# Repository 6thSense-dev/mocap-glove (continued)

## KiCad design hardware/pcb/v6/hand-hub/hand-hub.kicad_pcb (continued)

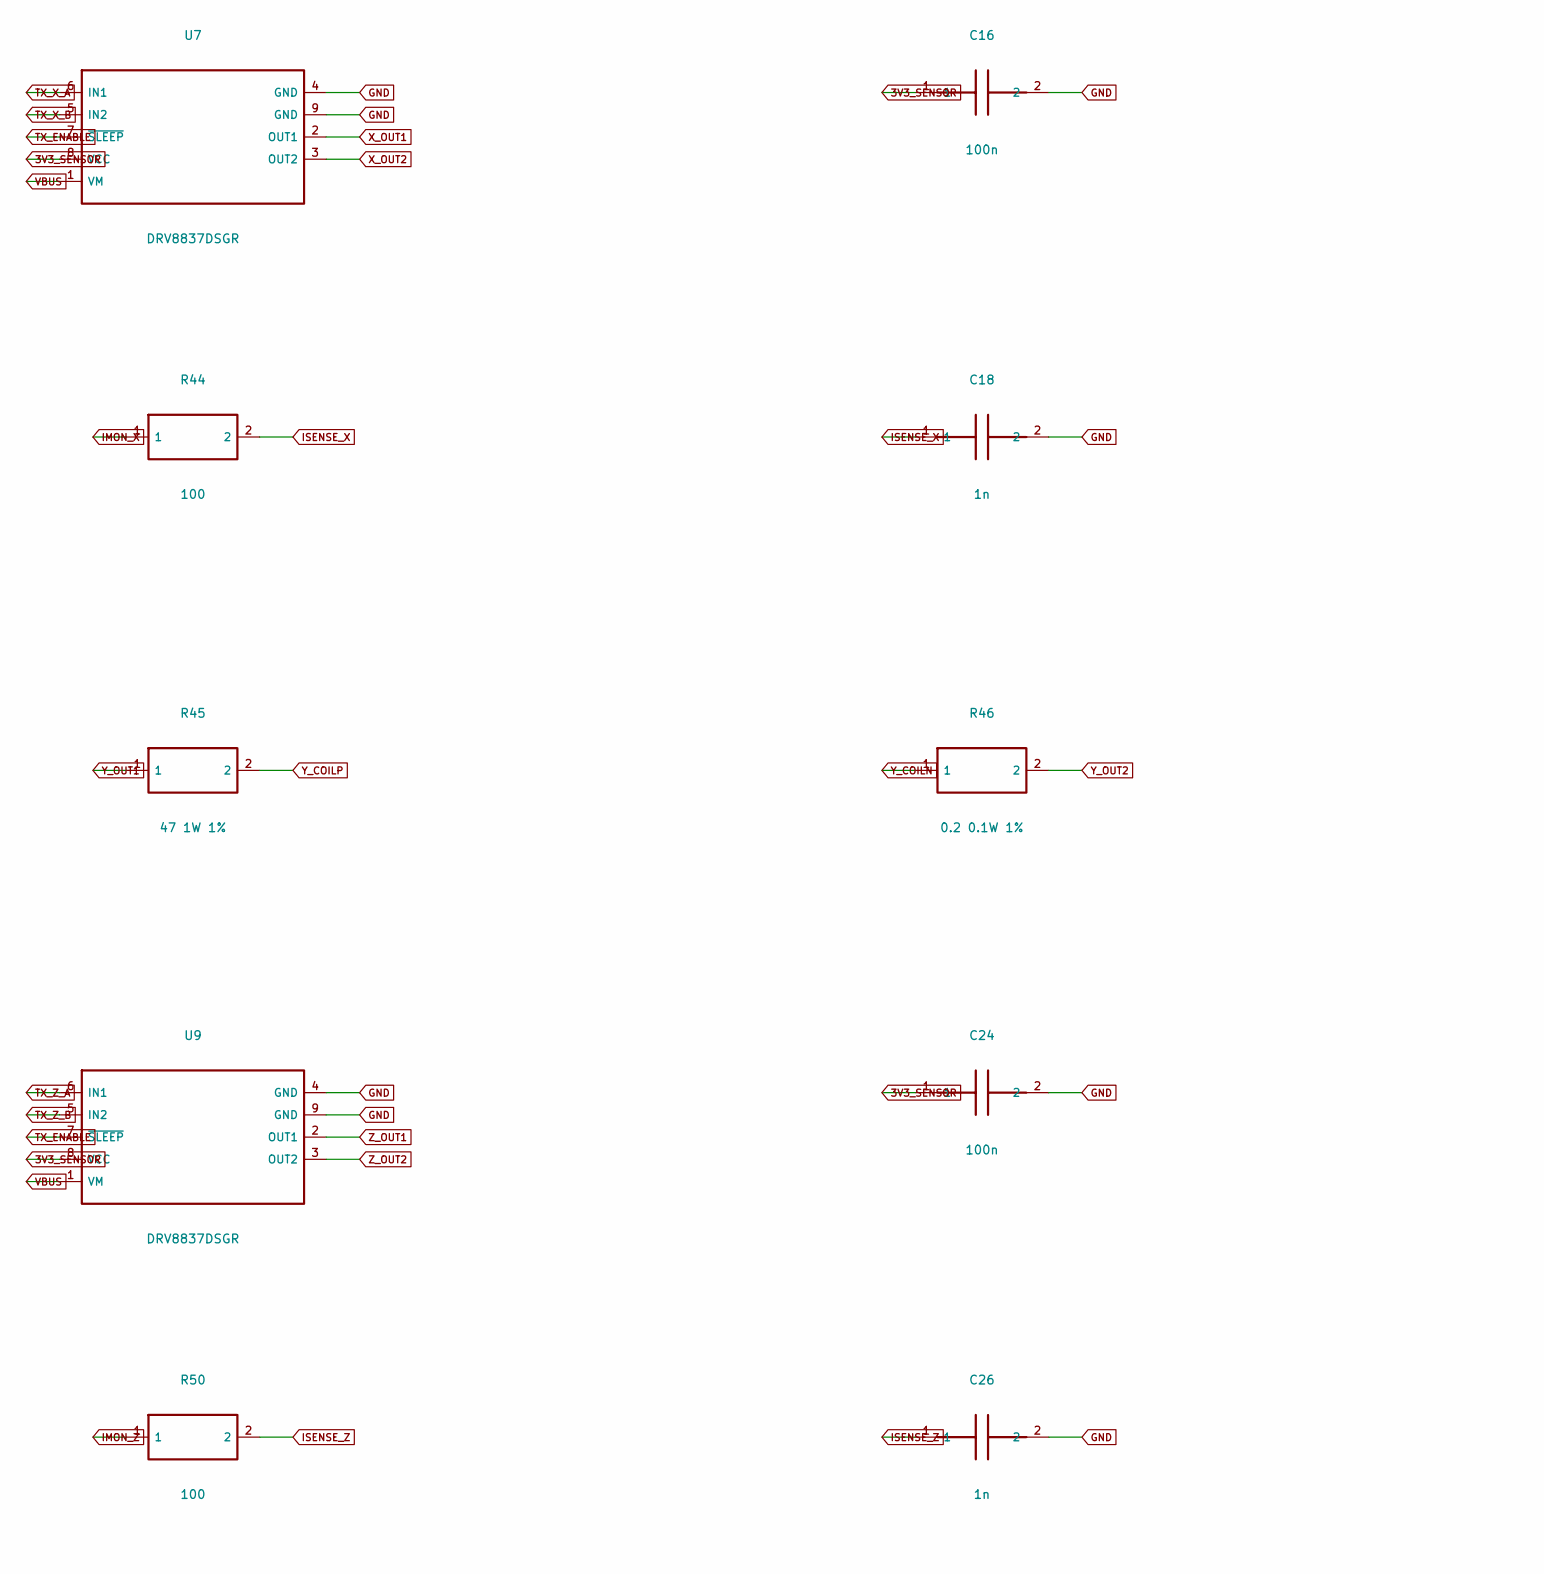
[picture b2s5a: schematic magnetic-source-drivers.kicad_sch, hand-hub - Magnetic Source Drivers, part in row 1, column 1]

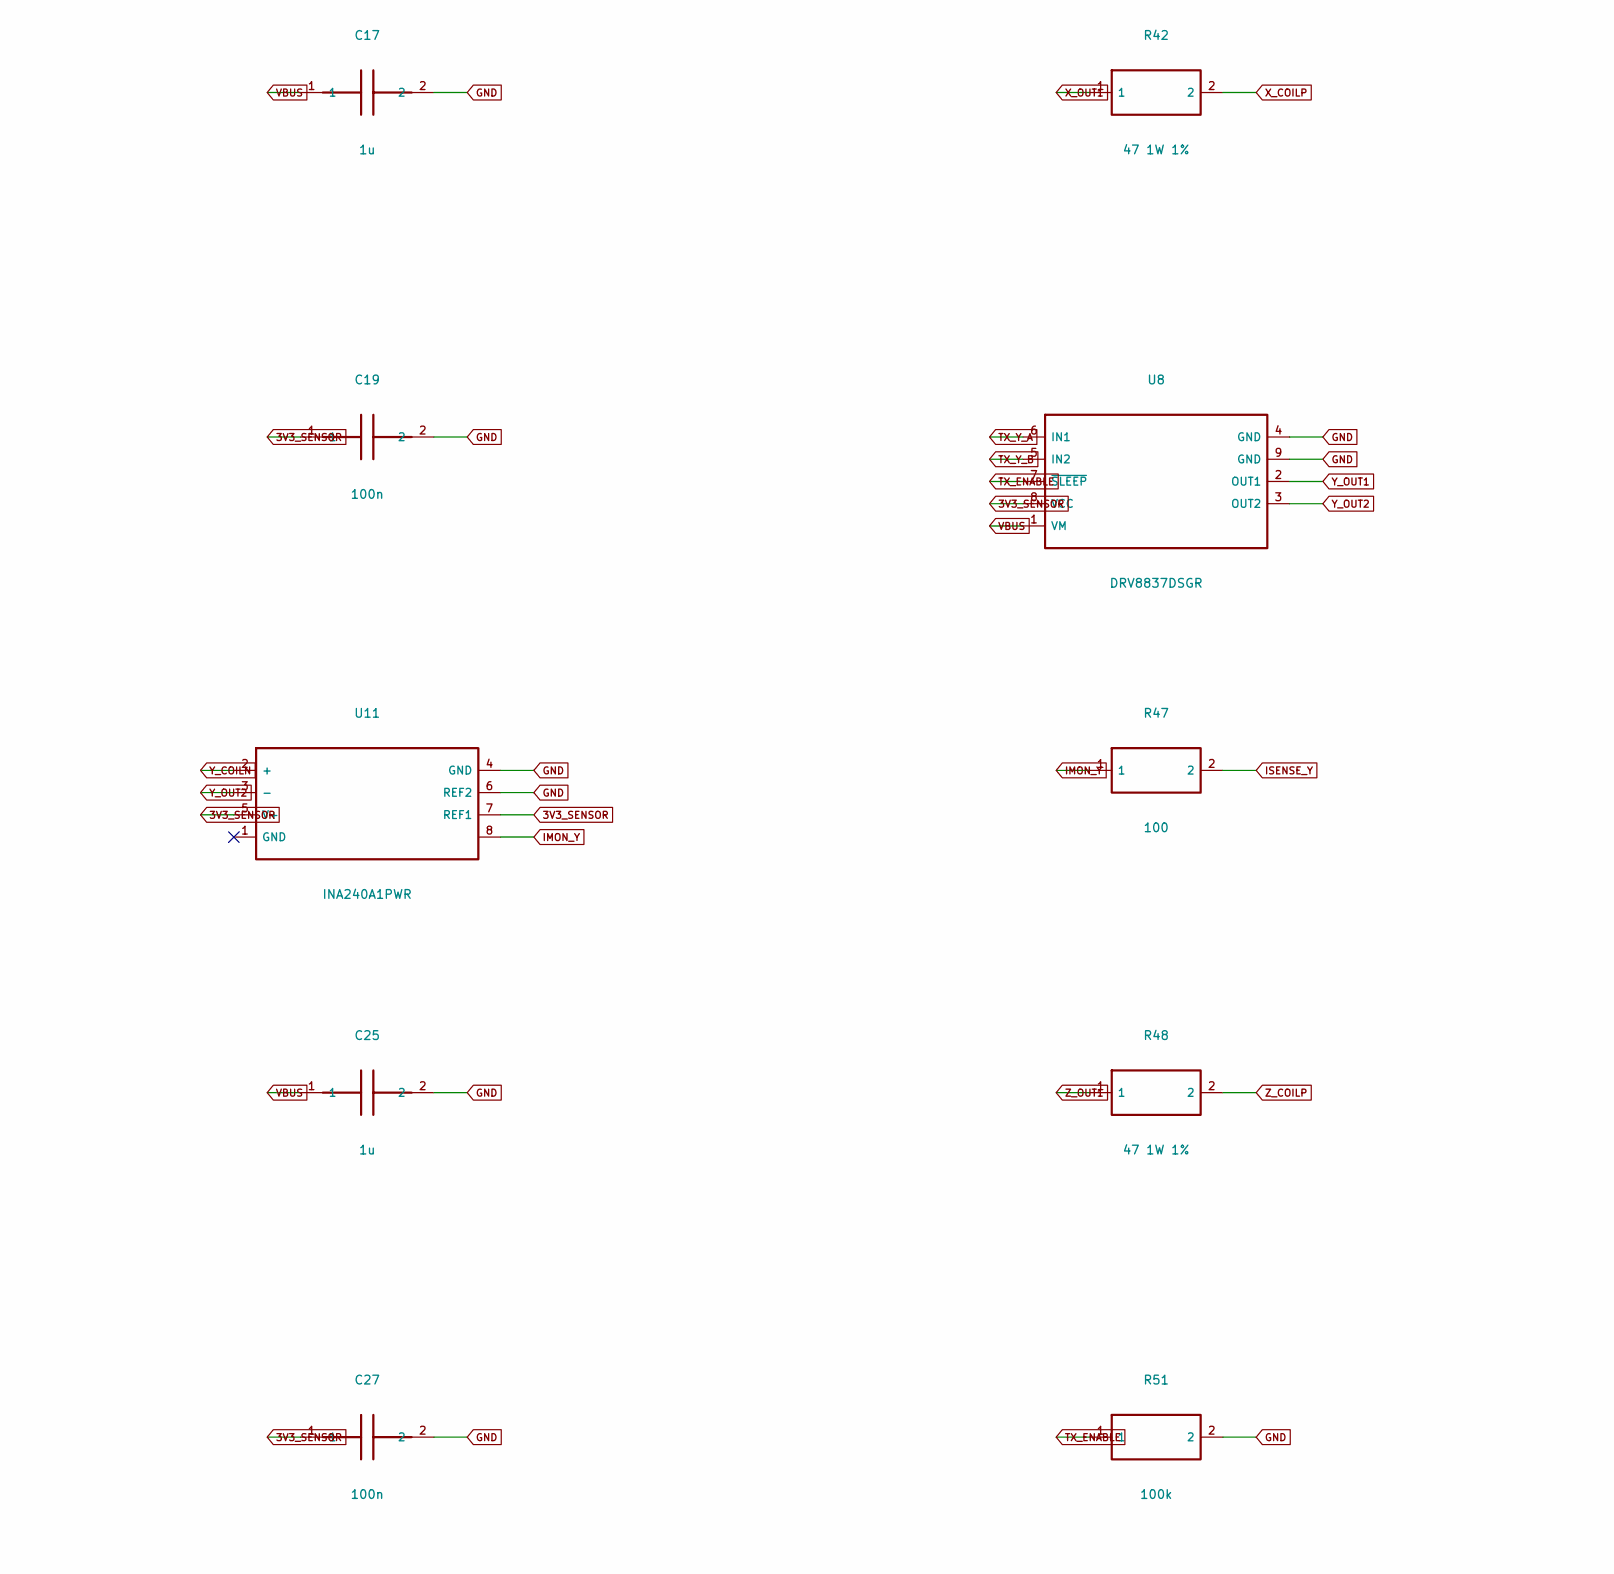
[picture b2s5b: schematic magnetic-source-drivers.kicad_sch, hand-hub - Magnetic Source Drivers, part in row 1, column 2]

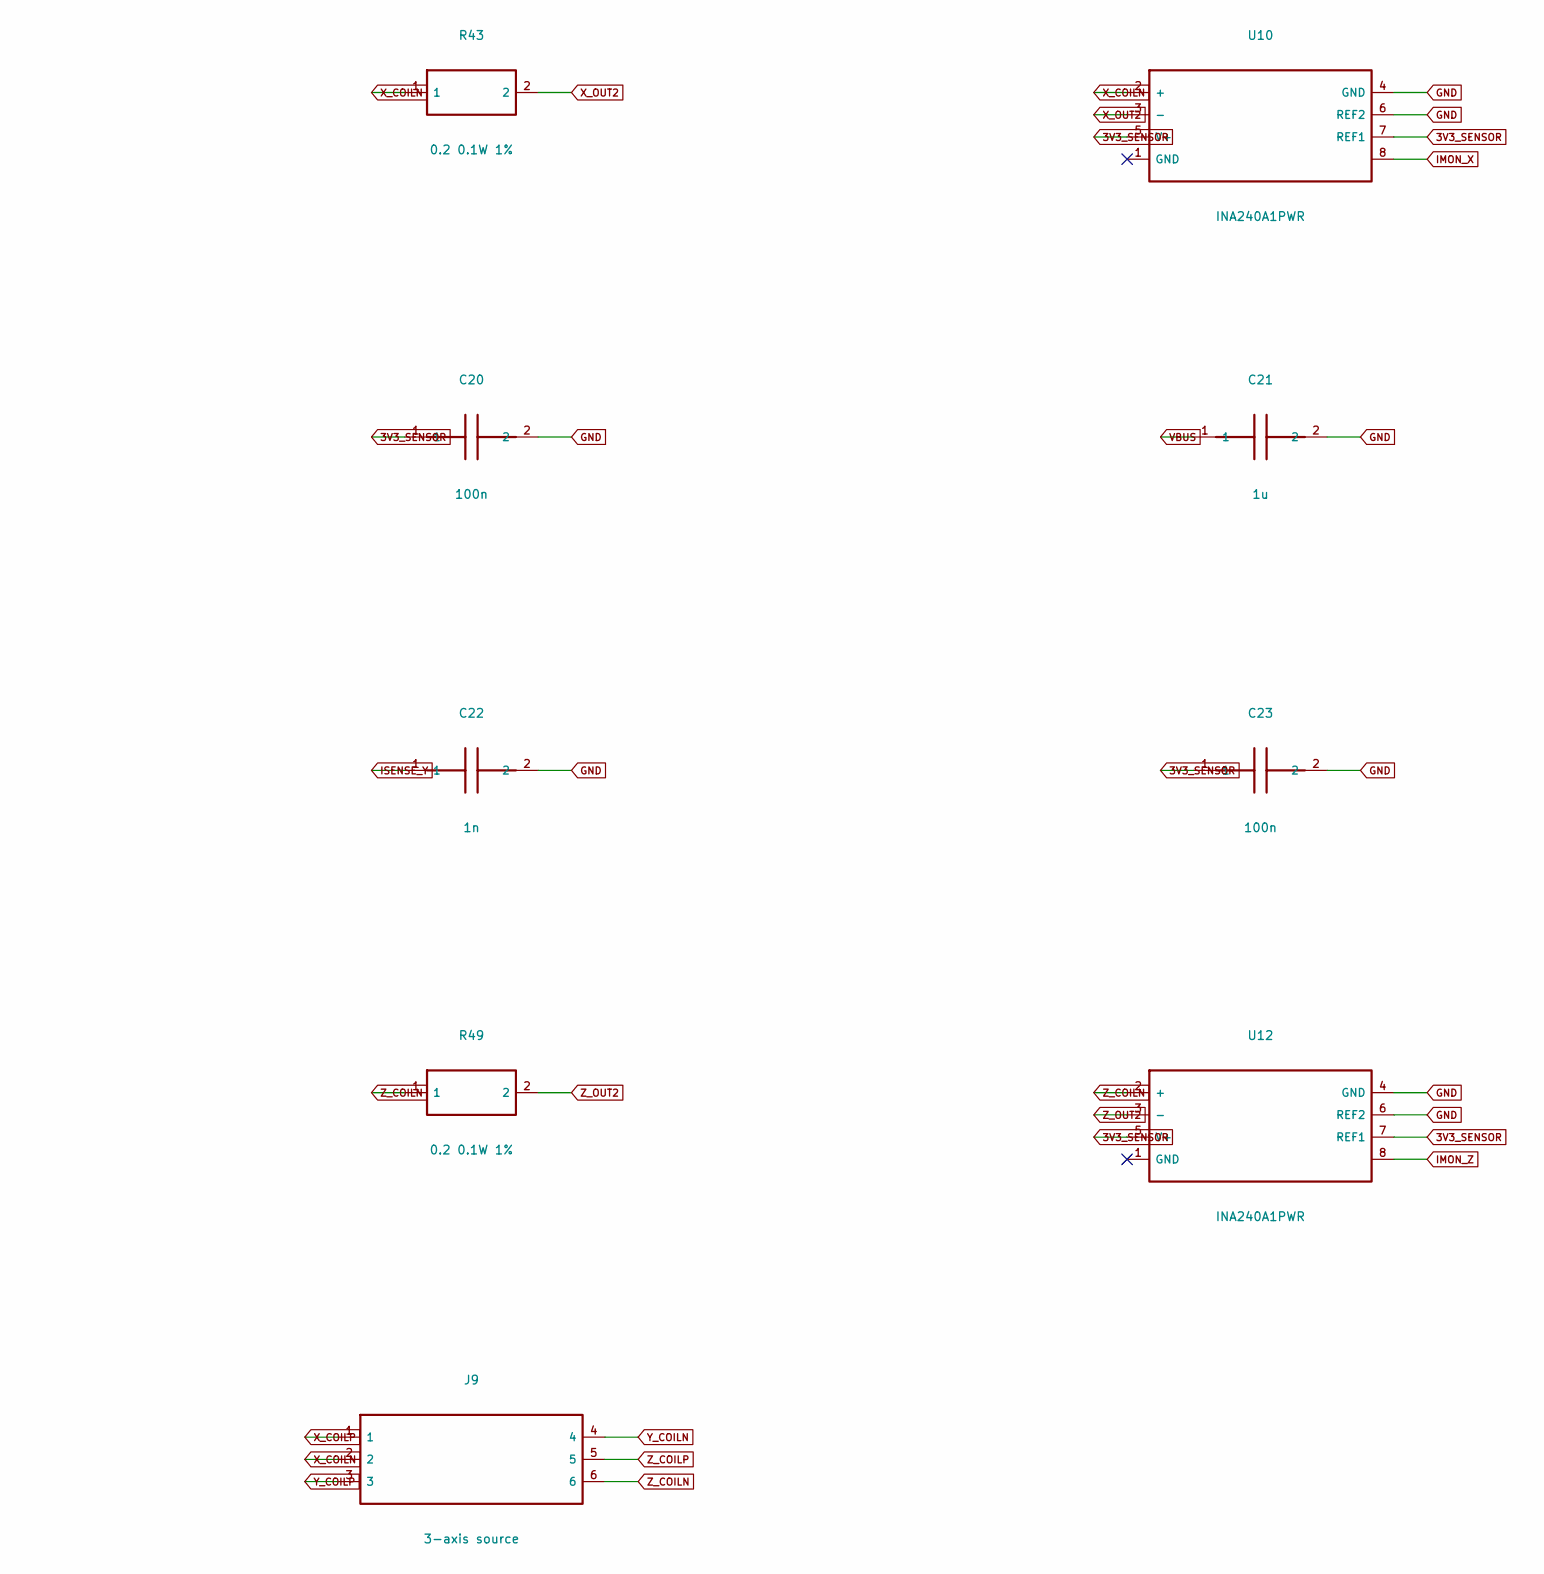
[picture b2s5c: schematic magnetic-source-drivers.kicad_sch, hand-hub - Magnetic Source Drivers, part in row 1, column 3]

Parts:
C16, C19, C20, C23, C24, C27: 100n; C_0402_1005Metric; MPN 100n
C17, C21, C25: 1u; C_0402_1005Metric; MPN 1u
C18, C22, C26: 1n; C_0402_1005Metric; MPN 1n
J9: 3-axis source; JST_SH_BM06B-SRSS-TB_1x06-1MP_P1.00mm_Vertical; MPN BM06B-SRSS-TB(LF)(SN)
R42, R45, R48: 47 1W 1%; R_2512_6332Metric; MPN FRR2512F47R0TS
R43, R46, R49: 0.2 0.1W 1%; R_0603_1608Metric; MPN RL0603FR-070R2L
R44, R47, R50: 100; R_0402_1005Metric; MPN 100
R51: 100k; R_0402_1005Metric; MPN 100k
U7, U8, U9: DRV8837DSGR; WSON-8-1EP_2x2mm_P0.5mm_EP0.9x1.6mm; MPN DRV8837DSGR
U10, U11, U12: INA240A1PWR; TSSOP-8_4.4x3mm_P0.65mm; MPN INA240A1PWR

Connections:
3V3_SENSOR: C16.1, C19.1, C20.1, C23.1, C24.1, C27.1, U7.8 (VCC), U8.8 (VCC), U9.8 (VCC), U10.5 (V+), U10.7 (REF1), U11.5 (V+), U11.7 (REF1), U12.5 (V+), U12.7 (REF1); also elsewhere on the board
GND: C16.2, C17.2, C18.2, C19.2, C20.2, C21.2, C22.2, C23.2, C24.2, C25.2, C26.2, C27.2, R51.2, U7.4 (GND), U7.9 (GND), U8.4 (GND), U8.9 (GND), U9.4 (GND), U9.9 (GND), U10.4 (GND), U10.6 (REF2), U11.4 (GND), U11.6 (REF2), U12.4 (GND), U12.6 (REF2); also elsewhere on the board
IMON_X: R44.1, U10.8
IMON_Y: R47.1, U11.8
IMON_Z: R50.1, U12.8
ISENSE_X: C18.1, R44.2; also elsewhere on the board
ISENSE_Y: C22.1, R47.2; also elsewhere on the board
ISENSE_Z: C26.1, R50.2; also elsewhere on the board
TX_ENABLE: R51.1, U7.7 (~SLEEP), U8.7 (~SLEEP), U9.7 (~SLEEP); also elsewhere on the board
TX_X_A: U7.6 (IN1); also elsewhere on the board
TX_X_B: U7.5 (IN2); also elsewhere on the board
TX_Y_A: U8.6 (IN1); also elsewhere on the board
TX_Y_B: U8.5 (IN2); also elsewhere on the board
TX_Z_A: U9.6 (IN1); also elsewhere on the board
TX_Z_B: U9.5 (IN2); also elsewhere on the board
VBUS: C17.1, C21.1, C25.1, U7.1 (VM), U8.1 (VM), U9.1 (VM); also elsewhere on the board
X_COILN: J9.2, R43.1, U10.2 (+)
X_COILP: J9.1, R42.2
X_OUT1: R42.1, U7.2 (OUT1)
X_OUT2: R43.2, U7.3 (OUT2), U10.3 (-)
Y_COILN: J9.4, R46.1, U11.2 (+)
Y_COILP: J9.3, R45.2
Y_OUT1: R45.1, U8.2 (OUT1)
Y_OUT2: R46.2, U8.3 (OUT2), U11.3 (-)
Z_COILN: J9.6, R49.1, U12.2 (+)
Z_COILP: J9.5, R48.2
Z_OUT1: R48.1, U9.2 (OUT1)
Z_OUT2: R49.2, U9.3 (OUT2), U12.3 (-)

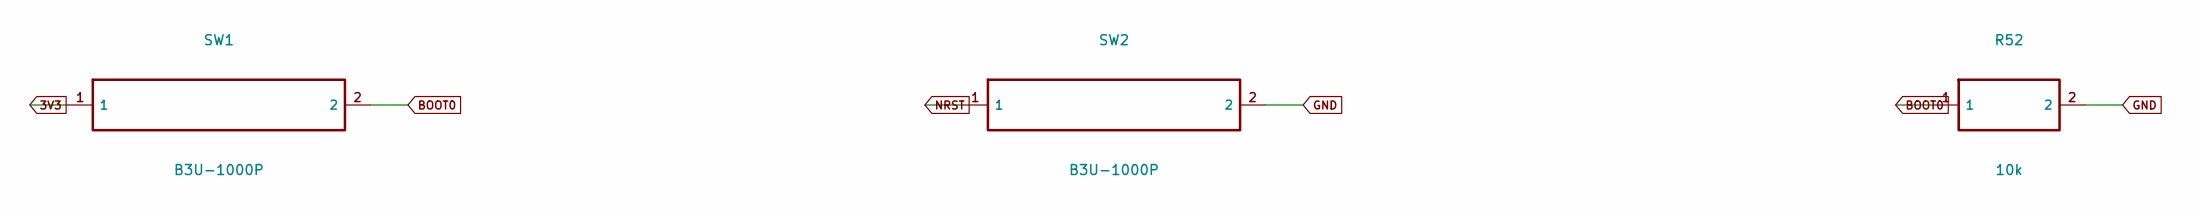
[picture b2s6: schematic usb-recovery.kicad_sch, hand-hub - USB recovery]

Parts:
R52: 10k; R_0402_1005Metric; MPN 10k
SW1, SW2: B3U-1000P; SW_SPST_B3U-1000P; MPN B3U-1000P

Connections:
3V3: SW1.1; also elsewhere on the board
BOOT0: R52.1, SW1.2; also elsewhere on the board
GND: R52.2, SW2.2; also elsewhere on the board
NRST: SW2.1; also elsewhere on the board

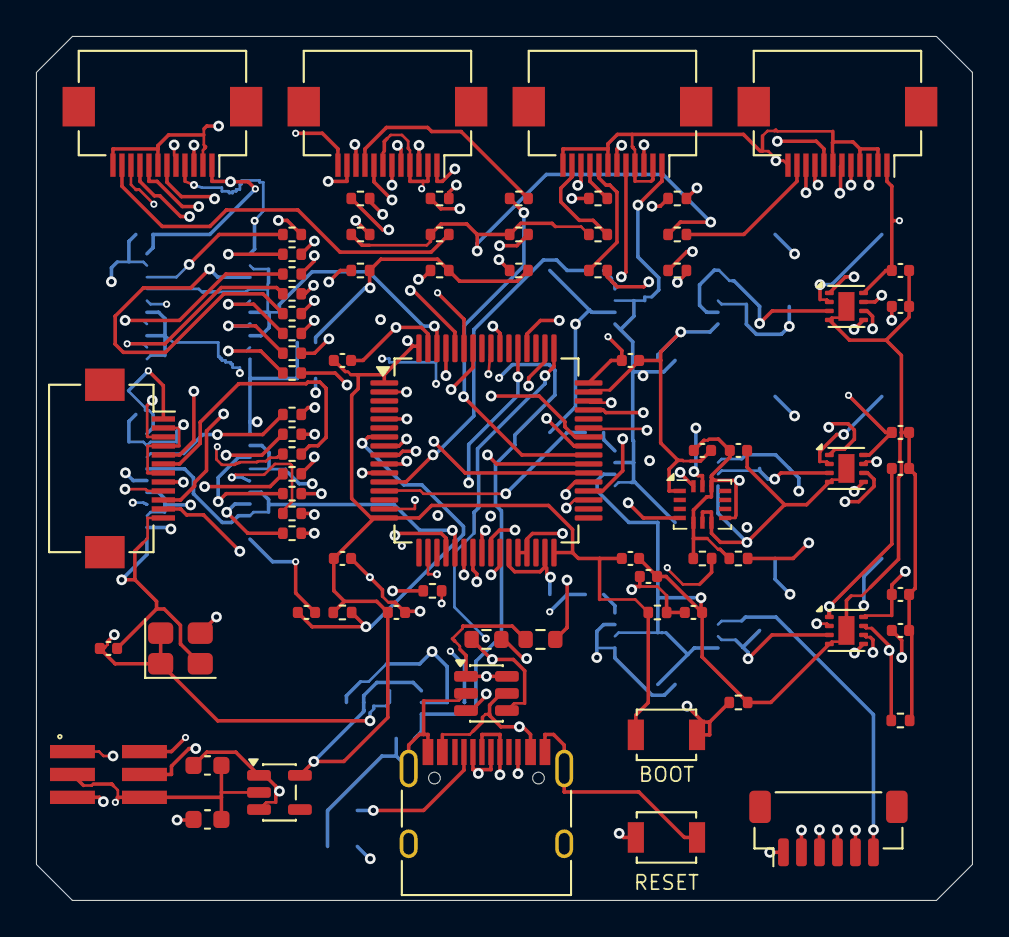
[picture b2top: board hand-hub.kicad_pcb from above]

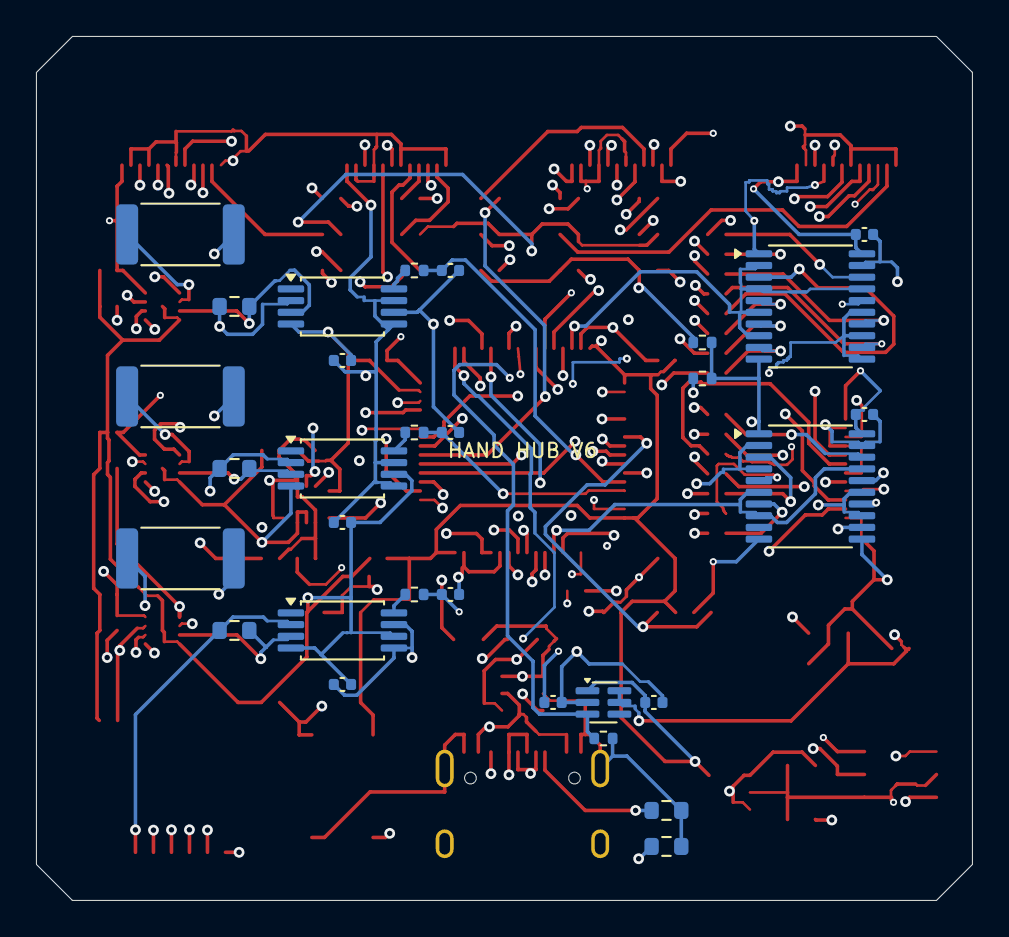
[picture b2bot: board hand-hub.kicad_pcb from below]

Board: 4 copper layers, 52.0 x 48.0 mm, 106 parts (30 on the bottom side), 109 nets.

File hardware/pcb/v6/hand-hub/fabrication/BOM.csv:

Comment,Designator,Footprint,LCSC Part #
TYPE-C-31-M-12,J6,USB_C_HRO_Envelope,C165948
5.1k,"R1,R2",R_0603_1608Metric,C23186
USBLC6-2SC6,U2,SOT-23-6,C7519
TLV75533PDBVR,U3,SOT-23-5,C404027
1u,C1,C_0603_1608Metric,C15849
4.7u,C2,C_0603_1608Metric,C19666
0,"R3,R4",R_0603_1608Metric,C21189
STM32G474RET6,U1,LQFP-64_10x10mm_P0.5mm,C521608
100n,"C10,C11,C12,C13,C14,C15,C16,C19,C20,C23,C24,C27,C28,C29,C3,C4,C5,C6,C9",C_0402_1005Metric,C1525
4.7u,C7,C_0402_1005Metric,C23733
10,R5,R_0402_1005Metric,C25077
1u,"C17,C21,C25,C8",C_0402_1005Metric,C52923
10k,"R52,R6",R_0402_1005Metric,C25744
PH1.27-02-03PWS,J7,XUNPU_PH127_2x03_SMD,C41360875
3N08192G33YC,Y1,SJK_3N_3225,C252332
33,"R25,R28,R31,R34,R37,R7",R_0402_1005Metric,C25105
120,"R10,R11,R12,R13,R14,R15,R16,R17,R18,R19,R20,R21,R22,R8,R9",R_0402_1005Metric,C114758
SN74LVC244APWR,"U4,U5",TSSOP-20_4.4x6.5mm_P0.65mm,C7668
FH12-12S-0.5SH(55),"J1,J2,J3,J4,J5",Hirose_FH12-12S-0.5SH_1x12-1MP_P0.50mm_Horizontal,C88360
47,"R23,R24,R26,R27,R29,R30,R32,R33,R35,R36",R_0402_1005Metric,C25118
100k,"R38,R39,R51,R53",R_0402_1005Metric,C25741
BMI323,U6,Bosch_LGA-14_3x2.5mm_P0.5mm,C5368700
4.7k,"R40,R41",R_0402_1005Metric,C25900
DRV8837DSGR,"U7,U8,U9",WSON-8-1EP_2x2mm_P0.5mm_EP0.9x1.6mm,C39159
FRR2512F47R0TS,"R42,R45,R48",R_2512_6332Metric,C49196864
RL0603FR-070R2L,"R43,R46,R49",R_0603_1608Metric,C723543
INA240A1PWR,"U10,U11,U12",TSSOP-8_4.4x3mm_P0.65mm,C93965
100,"R44,R47,R50",R_0402_1005Metric,C25076
1nF C0G 50V,"C18,C22,C26",C_0402_1005Metric,C307441
BM06B-SRSS-TB(LF)(SN),J9,JST_SH_BM06B-SRSS-TB_1x06-1MP_P1.00mm_Vertical,C160392
B3U-1000P,"SW1,SW2",SW_SPST_B3U-1000P,C231329
TPS22919DCKR,U14,SOT-363_SC-70-6,C2149796

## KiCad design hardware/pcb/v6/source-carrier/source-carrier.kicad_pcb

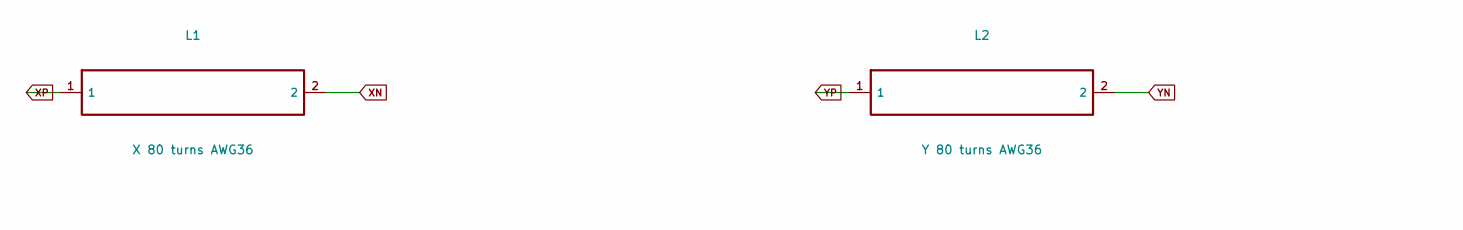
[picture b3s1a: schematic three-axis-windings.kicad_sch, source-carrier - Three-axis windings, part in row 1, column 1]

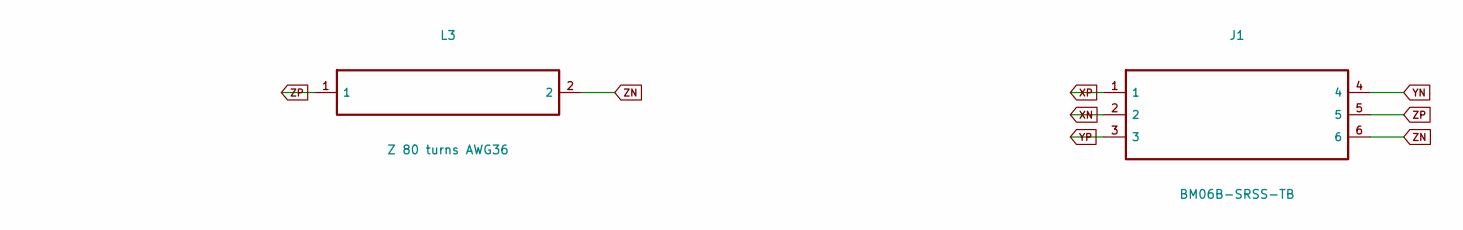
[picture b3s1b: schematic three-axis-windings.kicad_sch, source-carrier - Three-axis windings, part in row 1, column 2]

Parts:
J1: BM06B-SRSS-TB; JST_SH_BM06B-SRSS-TB_1x06-1MP_P1.00mm_Vertical; MPN BM06B-SRSS-TB(LF)(SN)
L1: X 80 turns AWG36; WirePair_SourceAssembly; MPN CUSTOM_WOUND_X
L2: Y 80 turns AWG36; WirePair; MPN CUSTOM_WOUND_Y
L3: Z 80 turns AWG36; WirePair; MPN CUSTOM_WOUND_Z

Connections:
XN: J1.2, L1.2
XP: J1.1, L1.1
YN: J1.4, L2.2
YP: J1.3, L2.1
ZN: J1.6, L3.2
ZP: J1.5, L3.1

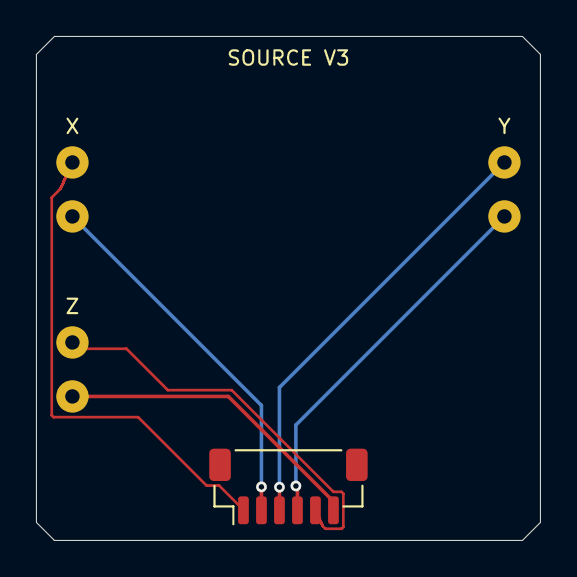
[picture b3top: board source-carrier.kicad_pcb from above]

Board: 2 copper layers, 28.0 x 28.0 mm, 4 parts (0 on the bottom side), 6 nets.
